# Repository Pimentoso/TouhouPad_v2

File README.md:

WARNING: THIS REPO IS STILL A WORK IN PROGRESS

Ergonomic gamepad to play Touhou Project games. Left-hand controls shoot/slow/bomb, and right hand controls movement. The bomb button is supposed to be pressed with the left thumb.

This is a newer version which uses a proper circuit board; for the old hand-wired version check here -> https://github.com/Pimentoso/TouhouPad

## Ordering the circuit board

- Go to https://jlcpcb.com/
- Create an account if needed.
- Click "order now"
- Upload the file `Archive.zip` you can find in the `kicad/gerber/` directory.
- Leave everything at default (you can change the pcb color if yolu want) and place the order. Note the minimum quantity you can order is 5

## Printing the enclosure

- You will need to 3d print the enclosure for the pad. You can find it in the `stl/` directory
- Print it face down without supports.
- In the top center of the plate there is a small hole. After you finish building the pad, you can stick a very small piece of transparent filament inside the hole to make the arduino power light shine through better.

(the circuit board in the picture is the prototype version)

## Building the pad

You will need
- Touhoupad circuit board (see above)
- 3d-printed enclosure
- Arduino pro micro board -> https://www.aliexpress.com/item/32888212119.html (the black one)
- 10x mx-style switches -> https://www.aliexpress.com/item/32899833333.html (gateron red or yellow are good for gaming)
- 10x keycaps -> https://www.aliexpress.com/item/32842379355.html (or just scavenge from an old mechanical keyboard)
- (optional) 4 silicone adhesive dots/feet
- (optional) a short RGB strip (ws2812b LEDs)

Solder the arduino to the circuit board. Place the circuit board inside the case, snap the switches in and solder them.

For RGB underglow: you can use the 3 exposed pins on the circuit board to solder a RGB strip. You can control the RGB lighting as follows

- Press esc+left arrow: toggle lighting on/off
- Press esc+right arrow: cycle lighting effects
- Press esc+up/down arrow: raise/lower brightness

Works better if you print the bottom part of the enclosure with transparent filament. Just pause the print at the 11mm mark and switch the filament to transparent.

## Flashing the firmware

- Method 1: flash `firmware/pimentoso_touhoupad_default.hex` using QMK Toolbox.
- Method 2: flash it directly using qmk firmware: `make pimentoso/touhoupad:default:flash`
- To enter bootloader mode: the bottom of the pad is completely exposed so you have access to the Arduino Pro micro. Just short together the RST and GND pins using a metal object to access bootloader mode.

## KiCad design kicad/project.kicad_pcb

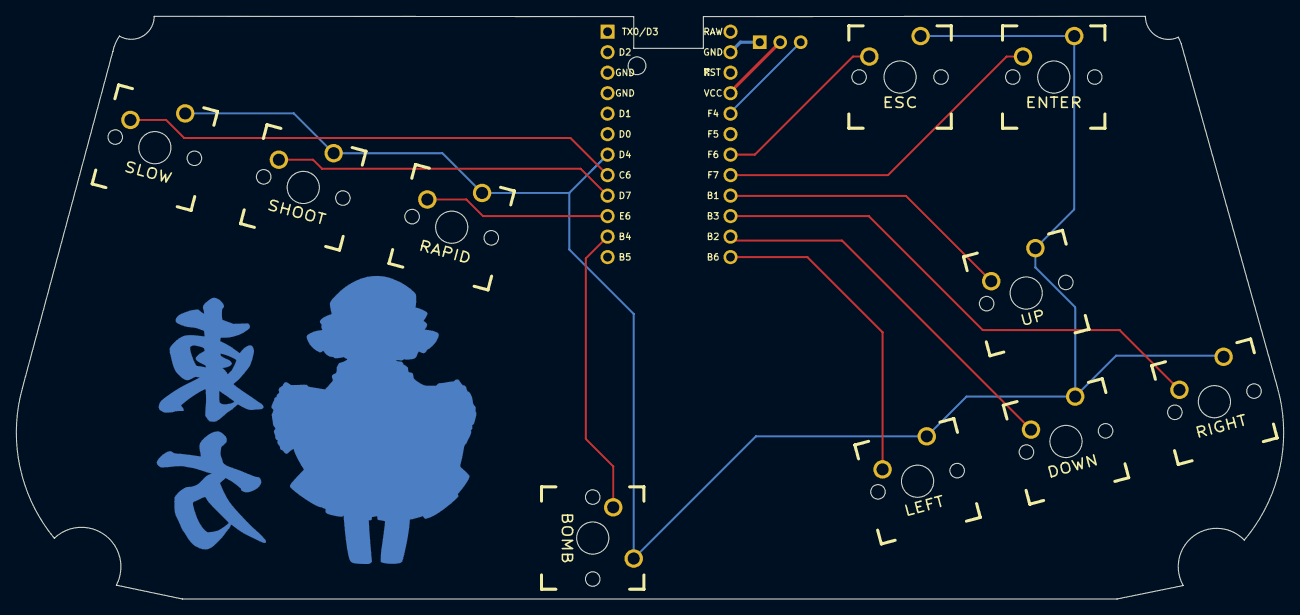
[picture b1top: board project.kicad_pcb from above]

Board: 2 copper layers, 157.1 x 72.2 mm, 12 parts (1 on the bottom side), 14 nets.

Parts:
BOMB: SW_DIP_x01; MX_PCB_100H
DOWN: SW_DIP_x01; MX_PCB_100H
ENTER: SW_DIP_x01; MX_PCB_100H
ESC: SW_DIP_x01; MX_PCB_100H
J0: Conn_01x03_Female; PinHeader_1x03_P2.54mm_Vertical
LEFT: SW_DIP_x01; MX_PCB_100H
RAPID: SW_DIP_x01; MX_PCB_100H
RIGHT: SW_DIP_x01; MX_PCB_100H
SHOOT: SW_DIP_x01; MX_PCB_100H
SLOW: SW_DIP_x01; MX_PCB_100H
U0: ProMicro here!; ArduinoProMicro
UP: SW_DIP_x01; MX_PCB_100H

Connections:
unnamed: J0.1, U0.23
unnamed: J0.2, U0.21
unnamed: J0.3, U0.20
unnamed: BOMB.1, DOWN.1, ENTER.1, ESC.1, LEFT.1, RAPID.1, RIGHT.1, SHOOT.1, SLOW.1, U0.7, UP.1
unnamed: SLOW.2, U0.8
unnamed: SHOOT.2, U0.9
unnamed: RAPID.2, U0.10
unnamed: BOMB.2, U0.11
unnamed: ESC.2, U0.18
unnamed: ENTER.2, U0.17
unnamed: LEFT.2, U0.13
unnamed: U0.16, UP.2
unnamed: DOWN.2, U0.14
unnamed: RIGHT.2, U0.15

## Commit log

2021-06-29 readme
2021-06-29 firmware json
2021-08-07 3d files
2021-08-07 firmware hex
2021-08-07 images and readme
2021-08-07 parts links in readme
2021-08-10 fix gerbers
